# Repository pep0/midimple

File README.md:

# midimple
Eurorack midi to cv module

## License

Hardware: cc-by-sa-3.0

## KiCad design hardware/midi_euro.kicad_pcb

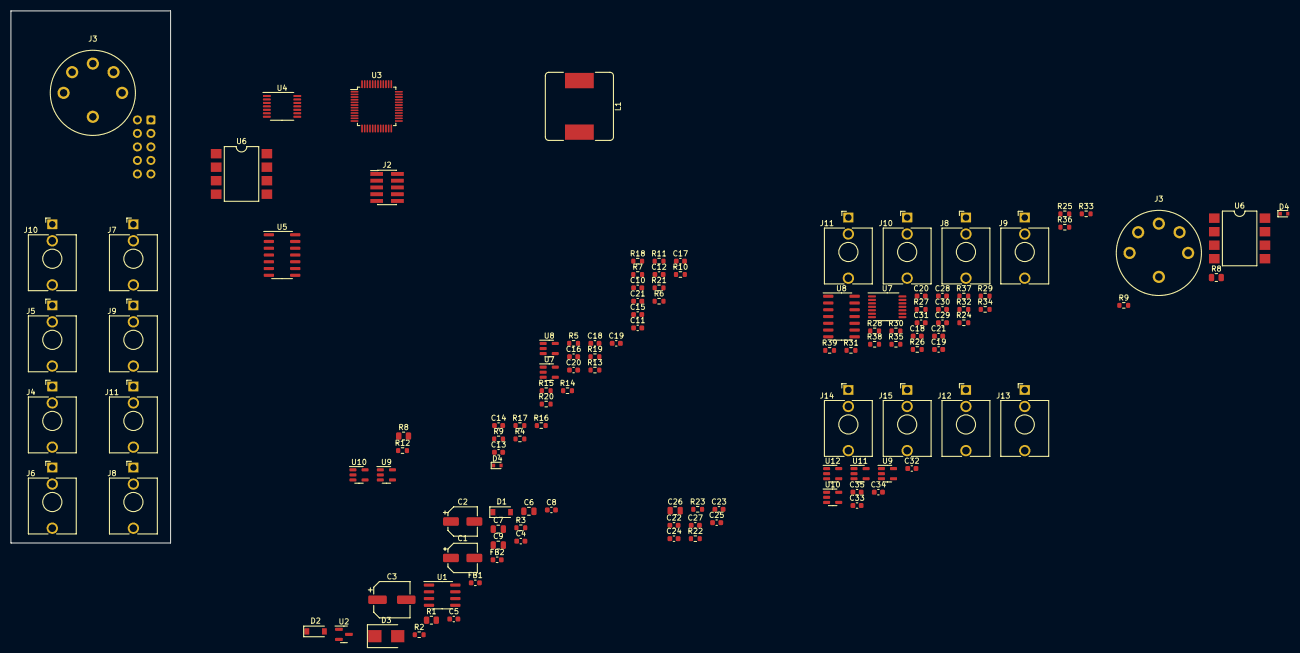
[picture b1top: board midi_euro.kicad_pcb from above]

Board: 2 copper layers, 30.0 x 100.0 mm, 125 parts (1 on the bottom side), 70 nets, no tracks yet.

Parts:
C1, C2: C_Polarized; CP_Elec_5x5.4
C3: 100uF; CP_Elec_6.3x7.7
C4, C5, C8, C10, C11, C12, C13, C18, C18#2, C19, C19#2, C20, C20#2, C21, C21#2, C32, C33, C34, C35: 100nF; C_0603_1608Metric
C6, C7, C9: 22uF; C_0805_2012Metric
C14, C15, C16, C17, C28, C29, C30, C31: 18p; C_0603_1608Metric
C22, C23, C24, C25, C27: 100n; C_0603_1608Metric
C26: 4.7uF; C_0805_2012Metric
D1, D2: MBR0540; D_SOD-123
D3: B220; D_SMB
D4, D4#2: 1N4148WT; D_SOD-523
FB1, FB2: FerriteBead; L_0603_1608Metric
J1: Conn_02x05_Top_Bottom; IDC-Header_2x05_P2.54mm_Vertical
J2: Conn_ARM_JTAG_SWD_10; PinHeader_2x05_P1.27mm_Vertical_SMD
J3, J3#2: CUI_SD-50BV
J4, J5, J6, J7, J8, J8#2, J9, J9#2, J10, J10#2, J11, J11#2, J12, J13, J14, J15: Thonkiconn; Jack_3.5mm_QingPu_WQP-PJ398SM_Vertical_CircularHoles
L1: SRR1260-221K; L_Bourns_SRR1260
R1: 0; R_0805_2012Metric
R2: 1Meg; R_0603_1608Metric
R3: 274k; R_0603_1608Metric
R4, R5, R24, R25: 5k; R_0603_1608Metric
R6, R7, R10, R11, R12, R13, R26, R27, R28, R29, R30, R31: 47k; R_0603_1608Metric
R8, R8#2: 220; R_0805_2012Metric
R9, R9#2: 10k; R_0603_1608Metric
R14, R15, R16, R17, R32, R33, R34, R35: 240k; R_0603_1608Metric
R18, R19, R20, R21, R36, R37, R38, R39: 1k; R_0603_1608Metric
R22: n.a.; R_0603_1608Metric
R23: 0; R_0603_1608Metric
U1: MAX5033B(A/U)SA; SOIC-8_3.9x4.9mm_P1.27mm
U2: LM3480-3.3; SOT-23
U3: STM32F030C8Tx; LQFP-48_7x7mm_P0.5mm
U4, U7: MAX5815; TSSOP-14_4.4x5mm_P0.65mm
U5, U8#2: TL074; SOIC-14_3.9x8.7mm_P1.27mm
U6, U6#2: 6N138; SMDIP-8_W9.53mm
U7#2, U8, U9, U9#2, U10, U10#2, U11, U12: 74AHC1G125; SOT-23-5

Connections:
+3V3: C8.2, C9.1, C11.1, C19.1, C22.1, C23.1, C24.1, C25.1, C26.1, J2.1 (VTref), R4.1, R5.1, R9.1, R9#2.1, R22.1, R24.1, R25.1, U2.1 (VO), U3.1 (VDD), U3.9 (VDDA), U4.9 (ADDR0), U4.13 (VDDIO), U4.14 (~LDAC), U6.8 (VCC), U6#2.8 (VCC), U7.9 (ADDR0), U7.13 (VDDIO), U7.14 (~LDAC)
+5V: C1.1, C6.1, C7.1, C10.1, C18.1, C18#2.1, C19#2.1, C20.1, C21.1, C32.1, C33.1, C34.1, C35.1, D1.1 (K), L1.2, R1.1, U1.4 (FB), U2.2 (VI), U4.7 (VDD), U7.7 (VDD), U7#2.5 (VCC), U8.5 (VCC), U9.5 (VCC), U9#2.5 (VCC), U10.5 (VCC), U10#2.5 (VCC), U11.5 (VCC), U12.5 (VCC)
/IOs/midi_rx: R9#2.2, U6.6 (VO2)
/controller/NRST: C27.1, J2.10 (~RESET), U3.7 (NRST)
/controller/SWCLK: J2.4 (SWDCLK/TCK), U3.37 (PA14)
/controller/SWDIO: J2.2 (SWDIO/TMS), U3.34 (PA13)
/controller/midi_rx: R9.2, U6#2.6 (VO2)
/pitch/I2C1_SCL: R5.2, U4.10 (SCL)
/pitch/I2C1_SDA: R4.2, U4.11 (SDA)
/pitch/dac_ref: R6.2, U4.1 (REF)
/pitch/dac_ref/2: R6.1, R7.2, U5.3 (+), U5.5 (+), U5.10 (+), U5.12 (+)
/velocity/I2C1_SCL: R25.2, U7.10 (SCL)
/velocity/I2C1_SDA: R24.2, U7.11 (SDA)
/velocity/dac_ref: R26.2, U7.1 (REF)
/velocity/dac_ref/2: R26.1, R27.2, U8#2.3 (+), U8#2.5 (+), U8#2.10 (+), U8#2.12 (+)
GND: C1.2, C2.1, C3.2, C4.1, C6.2, C7.2, C8.1, C9.2, C10.2, C11.2, C12.2, C13.1, C18.2, C18#2.2, C19.2, C19#2.2, C20.2, C20#2.2, C21.2, C21#2.1, C22.2, C23.2, C24.2, C25.2, C26.2, C27.2, C32.2, C33.2, C34.2, C35.2, D3.2 (A), J1.2, J1.3, J1.4, J1.7, J1.8, J1.9, J2.3 (GND), J2.5 (GND), J2.9 (GNDDetect), J4.S, J5.S, J6.S, J7.S, J8.S, J8#2.S, J9.S, J9#2.S, J10.S, J10#2.S, J11.S, J11#2.S, J12.S, J13.S, J14.S, J15.S, R3.2, R7.1, R23.2, R27.1, U1.3 (SGND), U1.6 (GND), U2.3 (GND), U3.8 (VSSA), U3.23 (VSS), U3.47 (VSS), U4.4 (GND), U4.8 (ADDR1), U6.5 (GND), U6#2.5 (GND), U7.4 (GND), U7.8 (ADDR1), U7#2.1, U7#2.3 (GND), U8.1, U8.3 (GND), U9.1, U9.3 (GND), U9#2.1, U9#2.3 (GND), U10.1, U10.3 (GND), U10#2.1, U10#2.3 (GND), U11.1, U11.3 (GND), U12.1, U12.3 (GND)
unnamed: C3.1, R1.2, R2.1, U1.7 (VIN)
unnamed: C4.2, U1.2 (VD)
unnamed: C5.1, U1.1 (BST)
unnamed: C5.2, D3.1 (K), L1.1, U1.8 (LX)
unnamed: C12.1, U5.4 (V+)
unnamed: C13.2, U5.11 (V-)
unnamed: C14.1, R10.2, R14.1, U5.2 (-)
unnamed: C14.2, R18.1, U5.1
unnamed: C15.1, R11.2, R15.1, U5.6 (-)
unnamed: C15.2, R19.1, U5.7
unnamed: C16.1, R12.2, R16.1, U5.9 (-)
unnamed: C16.2, R20.1, U5.8
unnamed: C17.1, R13.2, R17.1, U5.13 (-)
unnamed: C17.2, R21.1, U5.14
unnamed: C20#2.1, U8#2.4 (V+)
unnamed: C21#2.2, U8#2.11 (V-)
unnamed: C28.1, R28.2, R32.1, U8#2.2 (-)
unnamed: C28.2, R36.1, U8#2.1
unnamed: C29.1, R29.2, R33.1, U8#2.6 (-)
unnamed: C29.2, R37.1, U8#2.7
unnamed: C30.1, R30.2, R34.1, U8#2.9 (-)
unnamed: C30.2, R38.1, U8#2.8
unnamed: C31.1, R31.2, R35.1, U8#2.13 (-)
unnamed: C31.2, R39.1, U8#2.14
unnamed: D1.2 (A), FB1.1
unnamed: D2.1 (K), FB2.1
unnamed: D4.1 (K), D4#2.1 (K), R8.2, R8#2.2, U6.2 (C1), U6#2.2 (C1)
unnamed: D4.2 (A), D4#2.2 (A), J3.5, J3#2.5, U6.3 (C2), U6#2.3 (C2)
unnamed: FB1.2, J1.1, J1.6
unnamed: FB2.2, J1.5, J1.10
unnamed: J3.4, J3#2.4, R8.1, R8#2.1
unnamed: J4.T, R14.2, R18.2
unnamed: J5.T, R15.2, R19.2
unnamed: J6.T, R16.2, R20.2
unnamed: J7.T, R17.2, R21.2
unnamed: J8.T, J8#2.T, R32.2, R36.2, U7#2.4
unnamed: J9.T, J9#2.T, R33.2, R37.2, U8.4
unnamed: J10.T, J10#2.T, R34.2, R38.2, U9.4
unnamed: J11.T, J11#2.T, R35.2, R39.2, U10#2.4
unnamed: J12.T, U9#2.4
unnamed: J13.T, U10.4
unnamed: J14.T, U11.4
unnamed: J15.T, U12.4
unnamed: R2.2, R3.1, U1.5 (ON/~OFF)
unnamed: R10.1, U4.2 (OUTA)
unnamed: R11.1, U4.3 (OUTB)
unnamed: R12.1, U4.5 (OUTC)
unnamed: R13.1, U4.6 (OUTD)
unnamed: R22.2, R23.1, U3.44 (BOOT0)
unnamed: R28.1, U7.2 (OUTA)
unnamed: R29.1, U7.3 (OUTB)
unnamed: R30.1, U7.5 (OUTC)
unnamed: R31.1, U7.6 (OUTD)
VEE: C2.2, D2.2 (A)

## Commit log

2022-03-16 init kicad project
2022-03-16 MAX5715BAUD lib added
2023-01-26 chore: resync local state
